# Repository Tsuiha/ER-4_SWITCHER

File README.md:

# ER-4_SWITCHER

　「ER-4 SWITCHER」はEtymotic Reserch ER-4S, ER-4Bをリケーブルする際に使用できるネットワーク内蔵機器です。またスイッチを切り替えることでER-4S, ER-4Bの2種類のサウンドを楽しむことができます。  
 　ケーブル一体型の「Yスプリッタ」と、ステレオミニジャック接続用の「I, Uアダプタ」の3種類を製作しました。  
　ER-4筐体に加え、Yスプリッタは単体で、I, UアダプタはネットワークレスのリケーブルとICケーブルを別途用意することで、ER-4S, ER-4Bのリケーブルとして使用することができます。  
　組み立て済みのものは、ER-4Bタイプに切り替えた時に黒点が見えるようマーキングしてあります。入出力の方向性はありません。  

 　リポジトリに基板データと使用パーツが公開されています。 自由にしてください。
  
　[noteでも紹介しています](https://note.com/tsuiha/m/m1b87ad4bef4d)

*Yスプリッタ+リケーブル*

*Iアダプタ*

*Uアダプタ*

*PCB*

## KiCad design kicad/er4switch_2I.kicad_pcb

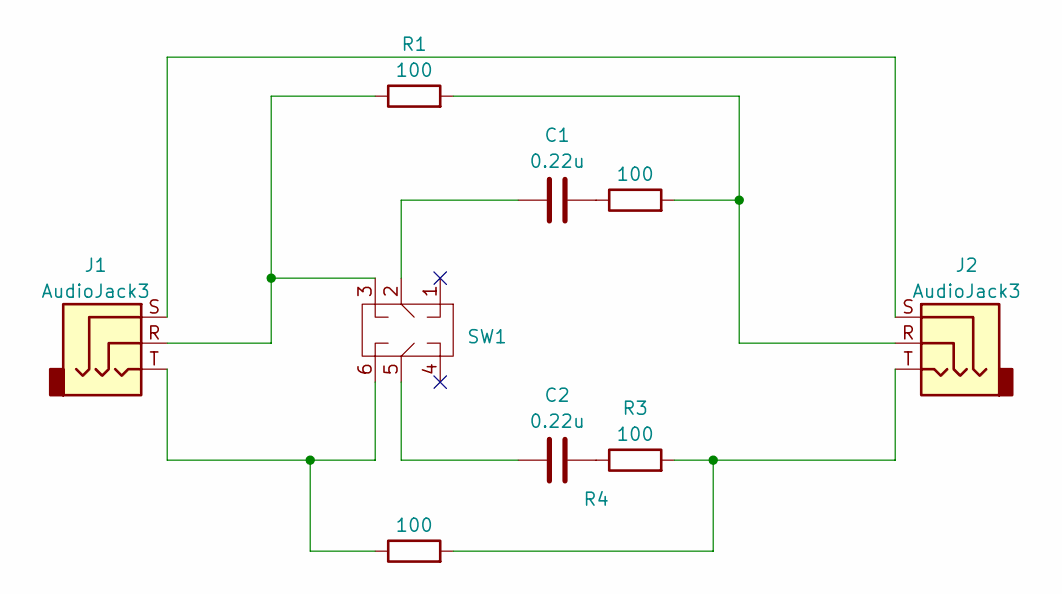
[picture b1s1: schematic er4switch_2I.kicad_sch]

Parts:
C1, C2: 0.22u; C_0805_2012Metric_Pad1.18x1.45mm_HandSolder
J1, J2: AudioJack3; Jack_3.5mm_Switronic_ST-005-G_horizontal
R1, R2, R3, R4: 100; R_0603_1608Metric_Pad0.98x0.95mm_HandSolder
SW1: CMS-2202TB

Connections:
unnamed: C1.1, SW1.2
unnamed: C1.2, R2.1
unnamed: C2.1, SW1.5
unnamed: C2.2, R3.1
unnamed: J1.R, R1.1, SW1.3
unnamed: J1.S, J2.S
unnamed: J1.T, R4.1, SW1.6
unnamed: J2.R, R1.2, R2.2
unnamed: J2.T, R3.2, R4.2

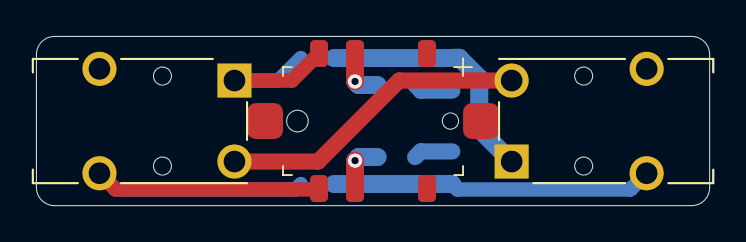
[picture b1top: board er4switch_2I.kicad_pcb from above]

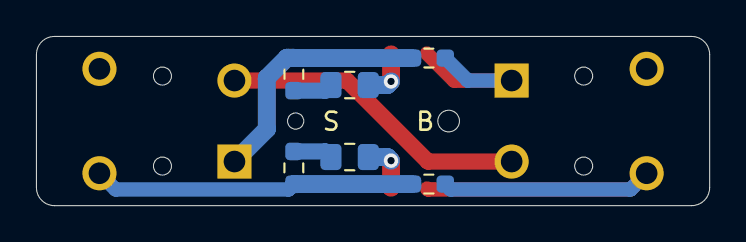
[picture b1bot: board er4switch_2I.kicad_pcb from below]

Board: 2 copper layers, 37.4 x 9.4 mm, 9 parts (6 on the bottom side), 9 nets.

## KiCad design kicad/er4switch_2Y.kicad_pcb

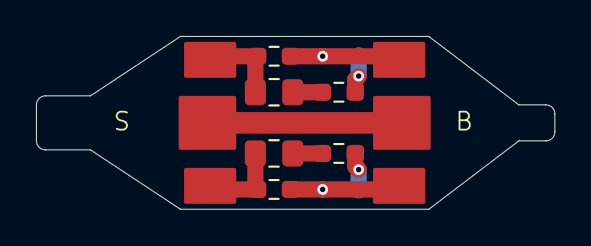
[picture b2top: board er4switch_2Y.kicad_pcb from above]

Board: 2 copper layers, 28.8 x 9.6 mm, 7 parts (1 on the bottom side), 8 nets.

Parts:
C1, C2: 0.22u; C_0805_2012Metric_Pad1.18x1.45mm_HandSolder
R1, R2, R3, R4: 100; R_0603_1608Metric_Pad0.98x0.95mm_HandSolder
SW1: CMS-2202TB_nopole

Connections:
unnamed: C1.1, R2.2
unnamed: C1.2, R1.2
unnamed: C2.1, R3.2
unnamed: C2.2, R4.2
unnamed: R1.1, SW1.5
unnamed: R4.1, SW1.2
unnamed: R2.1, SW1.6
unnamed: R3.1, SW1.3
